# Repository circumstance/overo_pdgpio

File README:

overo_pdgpio - PD External for GPIO input/output on Gumstix Overo systems

Copyright (C) 2012 Tim Redfern

This program is free software; you can redistribute it and/or modify it under the terms of the GNU Lesser
General Public License as published by the Free Software Foundation; either version 2.1 of the License,
or (at your option) any later version.

================================================================

overo_pdgpio allows the state of GPIO pins on the overo 40 pin breakout connector to be used for input and output from within PD (or PDa)

Information on these GPIOs is available here: 

http://gumstix.org/hardware-design/overo-coms/74-overo-connectors/97-gumstix-overo-series-40-pin-header.html

http://www.jumpnowtek.com/index.php?option=com_content&view=article&id=54&Itemid=60

According to this info there should be 3 outputs available to a standard overo:

GPIO144 (pin 30)
GPIO145 (pin 29)
GPIO170 (pin 19)

and 3 inputs:

GPIO114 (pin 4)
GPIO146 (pin27)
GPIO147 (pin 29)

However I wasn't able to get GPIO146 to work under Ubuntu 12.04

=================================================================
WARNING! DO NOT USE THIS SOFTWARE WITH ANY COMPUTER OTHER THAN A GUMSTIX OVERO
HARDWARE DAMAGE IS POSSIBLE BY MANIPULATION OF GPIO PORTS ON EMBEDDED SYSTEMS

To use- 

1. copy *.pd_linux and *.pd to:
        EITHER the same folder as your patch, or the PD extras folder (/usr/lib/pd/extra)

2. create an overo_gpioin or overo_gpiout object and look at the help file

3. see the schematic (eagle cad files) in the overo_controlboard folder for wiring details

=================================================================
overo_pdgpio was developed exclusively for circumstance - Tomorrow the ground forgets you were here

http://productofcircumstance.com/portfoliocpt/tomorrow-the-ground-forgets-you-were-here/

Bugs, issues, suggestions: tim@eclectronics.org

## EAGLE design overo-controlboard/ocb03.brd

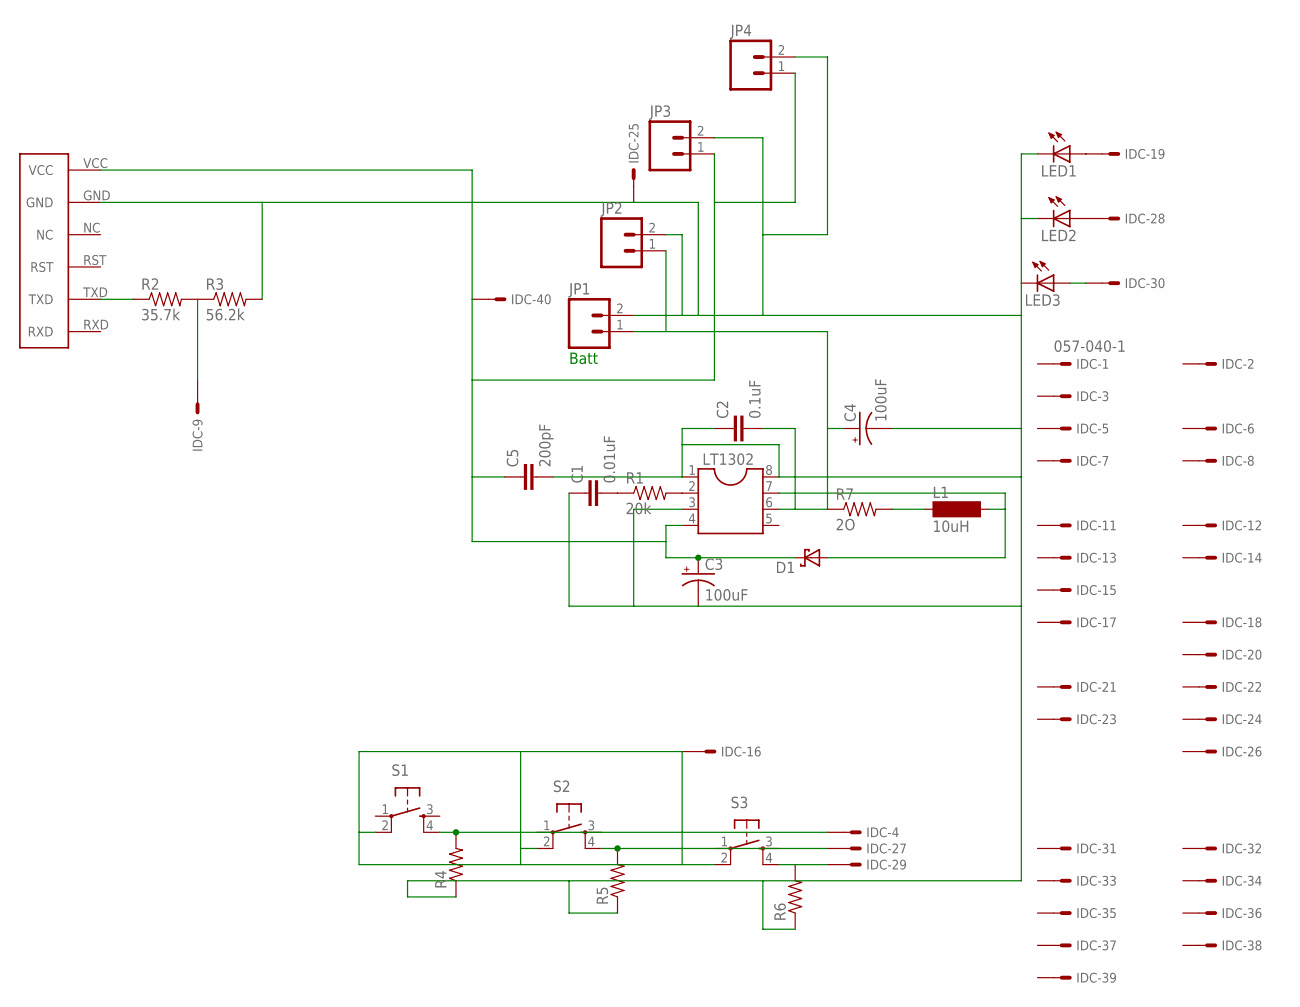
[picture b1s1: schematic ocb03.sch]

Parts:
C1: 0.01uF; CAP-PTH-SMALL
C2: 0.1uF; CAP-PTH-SMALL
C3, C4: 100uF; CPOL-RADIAL-100UF-25V
C5: 200pF; CAP-PTH-SMALL
D1: DS_E2L; E2LINE
IDC: 057-040-1
JP1, JP2, JP3, JP4: M02JST-PTH-2; JST-2-PTH
L1: 10uH; BS11
LED1, LED2, LED3: LED5MM
LT1302: DIL8; DIL08
R1: 20k; AXIAL-0.4
R2: 35.7k; AXIAL-0.4
R3: 56.2k; AXIAL-0.4
R4, R5, R6: RESISTORPTH-1/4W; AXIAL-0.4
R7: 2O; AXIAL-0.4
S1, S2, S3: TAC_SWITCHPTH; TACTILE-PTH
U$2: SKYLAB_LAB; SKYLAB_GPS

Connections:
GND: C1.1, C2.1, C3.2 (-), C4.2 (-), C5.2, IDC.25, JP1.2, JP2.2, JP3.2, JP4.2, LED1.K (C), LED2.K (C), LED3.K (C), LT1302.1, LT1302.3, LT1302.8, R3.P$2 (2), R4.P$1 (1), R5.P$1 (1), R6.P$1 (1), U$2.GND
unnamed: IDC.16, S1.2, S2.2, S3.2
unnamed: IDC.29, R6.P$2 (2), S3.4
unnamed: LT1302.2, R1.P$2 (2)
unnamed: C1.2, R1.P$1 (1)
unnamed: L1.1, R7.P$2 (2)
unnamed: IDC.19, LED1.A
unnamed: C2.2, C4.1 (+), JP1.1, JP2.1, LT1302.6, R7.P$1 (1)
unnamed: D1.2 (A), L1.2, LT1302.7
unnamed: IDC.28, LED2.A
unnamed: IDC.9, R2.P$2 (2), R3.P$1 (1)
unnamed: IDC.27, R5.P$2 (2), S2.4
unnamed: IDC.4, R4.P$2 (2), S1.4
unnamed: IDC.30, LED3.A
unnamed: C3.1 (+), C5.1, D1.1 (K), IDC.40, JP3.1, JP4.1, LT1302.4, U$2.VCC
unnamed: R2.P$1 (1), U$2.TXD

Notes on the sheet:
Batt

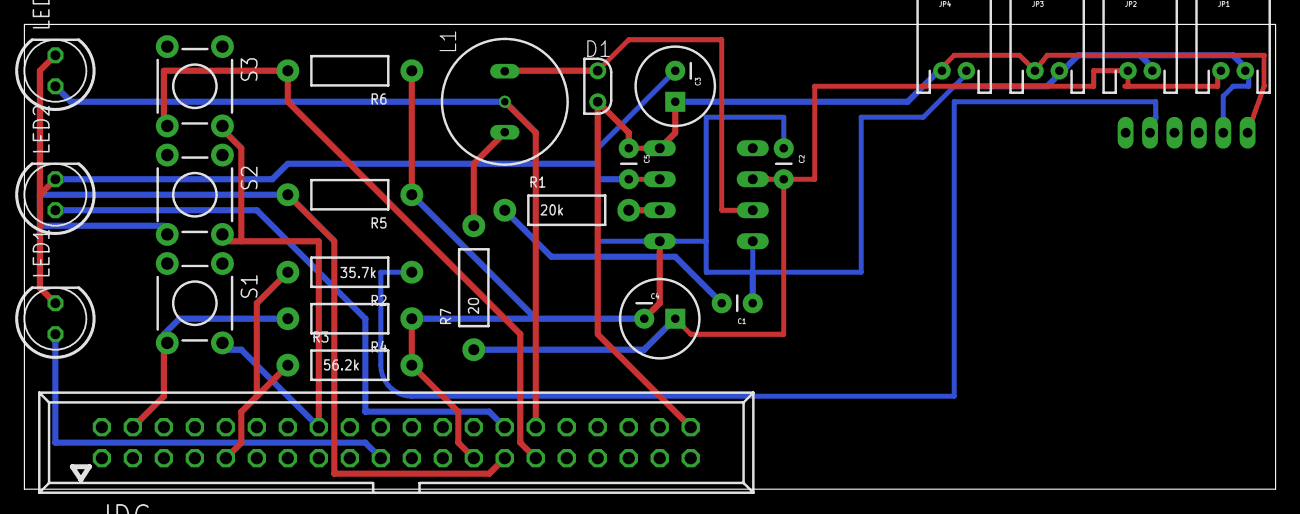
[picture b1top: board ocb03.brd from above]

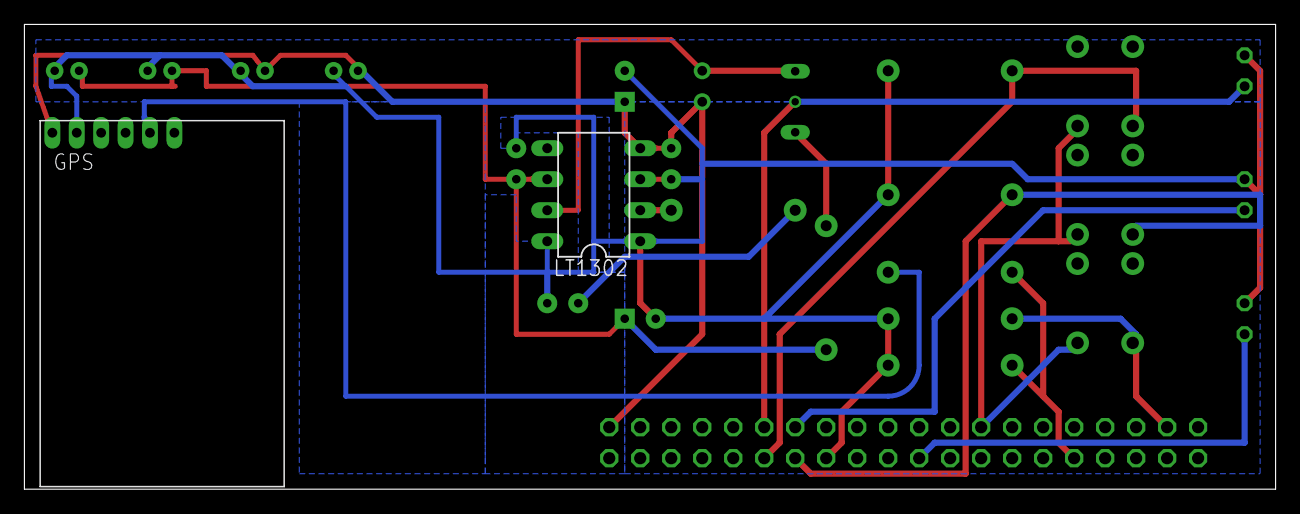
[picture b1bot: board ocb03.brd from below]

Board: 2 copper layers, 102.5 x 38.1 mm, 27 parts (2 on the bottom side), 16 nets.

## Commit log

2012-06-07 added output external
2012-06-07 fixed direction bug output
2012-06-07 compiled plugins
2012-06-08 fixed leds bug binaries
2012-09-13 releasing
